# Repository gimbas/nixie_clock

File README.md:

# Nixie Clock

yet another nixie tube clock, esp32 wifi enabled, temperature and humidity sensing, air quality sensing.

## Built With

* esp-idf
* eagle cad

## Authors

* **Rafael Silva** - *initial work* - [gimbas](https://github.com/gimbas)

See also the list of [contributors](https://github.com/gimbas/nixie_clock/graphs/contributors) who participated in this project.

## License

<br />This work is licensed under a <a rel="license" href="http://creativecommons.org/licenses/by-sa/4.0/">Creative Commons Attribution-ShareAlike 4.0 International License</a>.

## Acknowledgments

* HV power supply development and testing - [tonyp7](https://github.com/tonyp7/)

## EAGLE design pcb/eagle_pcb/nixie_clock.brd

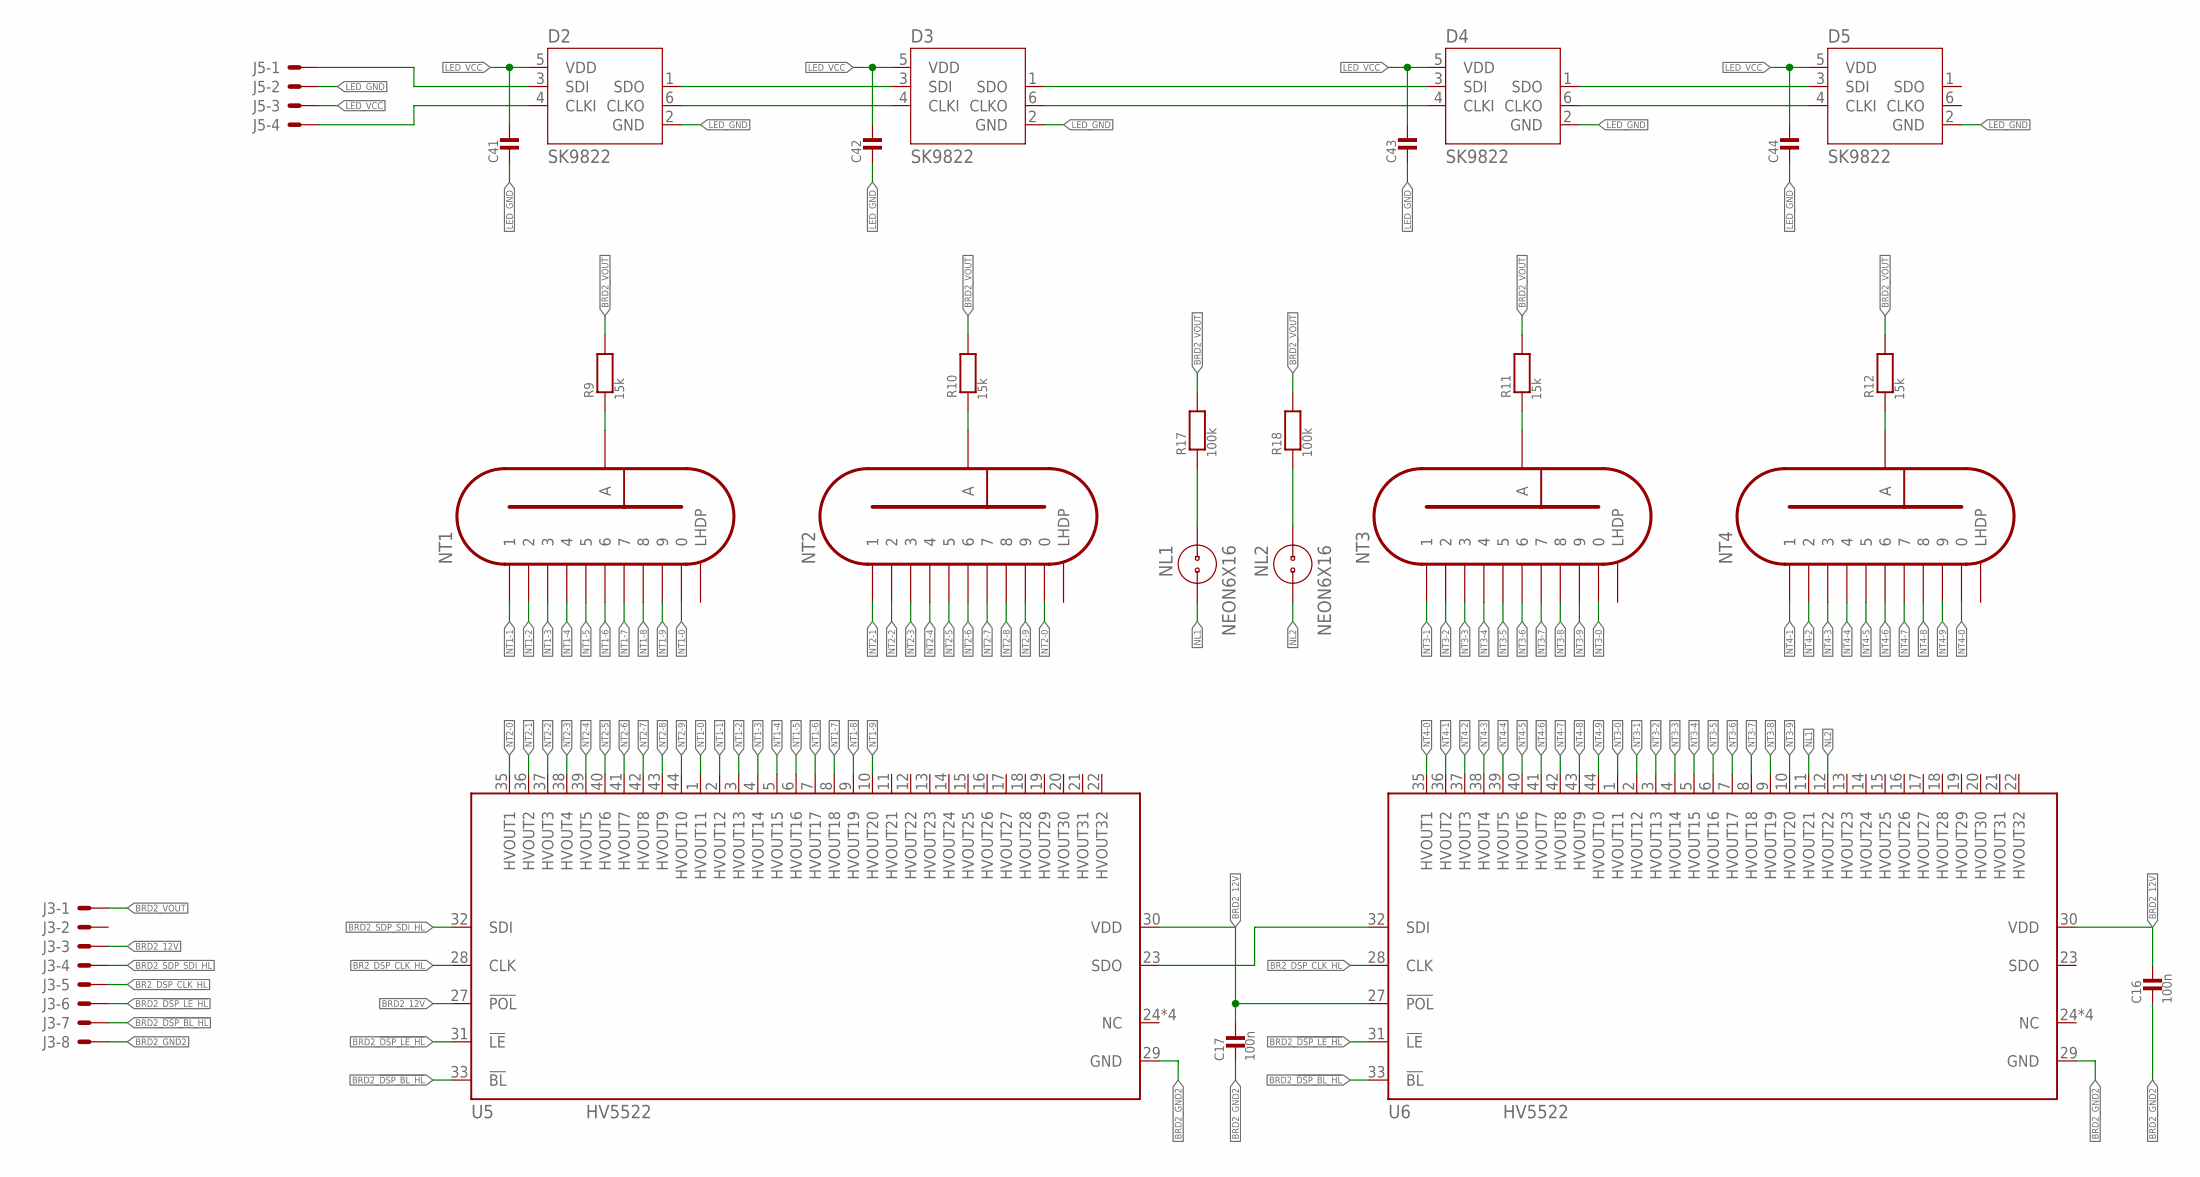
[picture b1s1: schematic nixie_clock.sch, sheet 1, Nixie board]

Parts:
C16, C17: 100n; 0603_WAVE
C41, C42, C43, C44: MLCC0603; 0603_WAVE
D2, D3, D4, D5: SK9822; 2020
J3: 8; 1X8_2.54
J5: 4; 1X4_2.54
NL1, NL2: NEON6X16; NL-6X16
NT1, NT2, NT3, NT4: IN-12B; IN-12
R9, R10, R11, R12: 15k; _1206
R17, R18: 100k; _1206
U5, U6: HV5522; QFP64

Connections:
BR2_DSP_CLK_HL: J3.5, U5.28 (CLK), U6.28 (CLK)
BRD2_12V: C16.P$1, C17.P$1, J3.3, U5.27 (!POL), U5.30 (VDD), U6.27 (!POL), U6.30 (VDD)
BRD2_!DSP_BL_HL: J3.7, U5.33 (!BL), U6.33 (!BL)
BRD2_!DSP_LE_HL: J3.6, U5.31 (!LE), U6.31 (!LE)
BRD2_GND2: C16.P$2, C17.P$2, J3.8, U5.29 (GND), U6.29 (GND)
BRD2_SDP_SDI_HL: J3.4, U5.32 (SDI)
BRD2_VOUT: J3.1, R9.2, R10.2, R11.2, R12.2, R17.2, R18.2
LED_GND: C41.P$2, C42.P$2, C43.P$2, C44.P$2, D2.2 (GND), D3.2 (GND), D4.2 (GND), D5.2 (GND), J5.2
LED_VCC: C41.P$1, C42.P$1, C43.P$1, C44.P$1, D2.5 (VDD), D3.5 (VDD), D4.5 (VDD), D5.5 (VDD), J5.3
unnamed: NT1.A, R9.1
unnamed: NT2.A, R10.1
unnamed: NT3.A, R11.1
unnamed: NT4.A, R12.1
unnamed: NL1.1, R17.1
unnamed: NL2.1, R18.1
unnamed: U5.23 (SDO), U6.32 (SDI)
unnamed: D2.3 (SDI), J5.1
unnamed: D2.4 (CLKI), J5.4
unnamed: D3.1 (SDO), D4.3 (SDI)
unnamed: D3.6 (CLKO), D4.4 (CLKI)
unnamed: D4.6 (CLKO), D5.4 (CLKI)
unnamed: D4.1 (SDO), D5.3 (SDI)
unnamed: D2.6 (CLKO), D3.4 (CLKI)
unnamed: D2.1 (SDO), D3.3 (SDI)
NL1: NL1.2, U6.11 (HVOUT21)
NL2: NL2.2, U6.12 (HVOUT22)
NT1-0: NT1.0, U5.1 (HVOUT11)
NT1-1: NT1.1, U5.2 (HVOUT12)
NT1-2: NT1.2, U5.3 (HVOUT13)
NT1-3: NT1.3, U5.4 (HVOUT14)
NT1-4: NT1.4, U5.5 (HVOUT15)
NT1-5: NT1.5, U5.6 (HVOUT16)
NT1-6: NT1.6, U5.7 (HVOUT17)
NT1-7: NT1.7, U5.8 (HVOUT18)
NT1-8: NT1.8, U5.9 (HVOUT19)
NT1-9: NT1.9, U5.10 (HVOUT20)
NT2-0: NT2.0, U5.35 (HVOUT1)
NT2-1: NT2.1, U5.36 (HVOUT2)
NT2-2: NT2.2, U5.37 (HVOUT3)
NT2-3: NT2.3, U5.38 (HVOUT4)
NT2-4: NT2.4, U5.39 (HVOUT5)
NT2-5: NT2.5, U5.40 (HVOUT6)
NT2-6: NT2.6, U5.41 (HVOUT7)
NT2-7: NT2.7, U5.42 (HVOUT8)
NT2-8: NT2.8, U5.43 (HVOUT9)
NT2-9: NT2.9, U5.44 (HVOUT10)
NT3-0: NT3.0, U6.1 (HVOUT11)
NT3-1: NT3.1, U6.2 (HVOUT12)
NT3-2: NT3.2, U6.3 (HVOUT13)
NT3-3: NT3.3, U6.4 (HVOUT14)
NT3-4: NT3.4, U6.5 (HVOUT15)
NT3-5: NT3.5, U6.6 (HVOUT16)
NT3-6: NT3.6, U6.7 (HVOUT17)
NT3-7: NT3.7, U6.8 (HVOUT18)
NT3-8: NT3.8, U6.9 (HVOUT19)
NT3-9: NT3.9, U6.10 (HVOUT20)
NT4-0: NT4.0, U6.35 (HVOUT1)
NT4-1: NT4.1, U6.36 (HVOUT2)
NT4-2: NT4.2, U6.37 (HVOUT3)
NT4-3: NT4.3, U6.38 (HVOUT4)
NT4-4: NT4.4, U6.39 (HVOUT5)
NT4-5: NT4.5, U6.40 (HVOUT6)
NT4-6: NT4.6, U6.41 (HVOUT7)
NT4-7: NT4.7, U6.42 (HVOUT8)
NT4-8: NT4.8, U6.43 (HVOUT9)
NT4-9: NT4.9, U6.44 (HVOUT10)

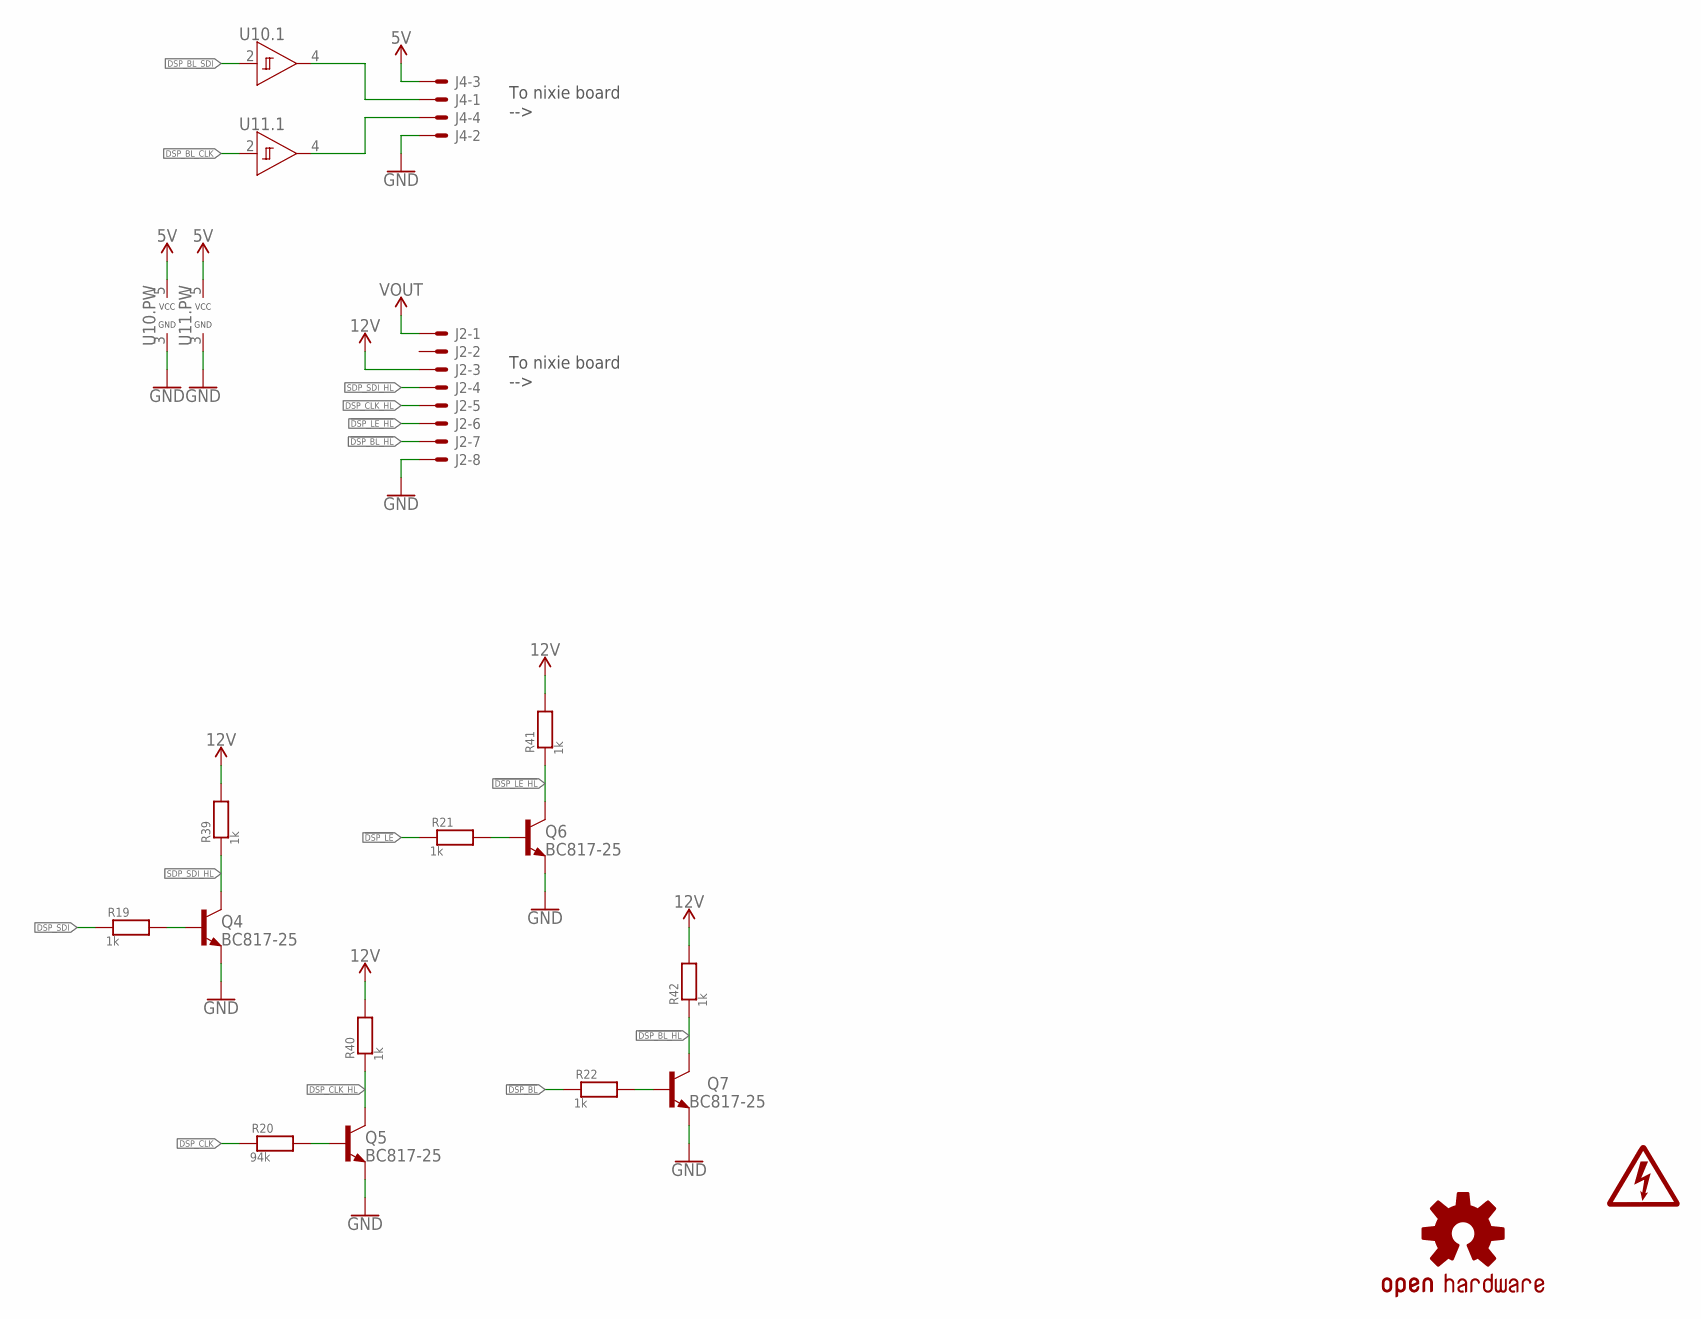
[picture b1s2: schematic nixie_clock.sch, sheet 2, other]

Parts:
J2: 8; 1X8_2.54
J4: 4; 1X4_2.54
LOGO3: OSHW-LOGOL; OSHW-LOGO-L
LOGO6: HV_WARNING
Q4, Q5, Q6, Q7: BC817-25; SOT-23-3
R19, R21, R22, R39, R40, R41, R42: 1k; 0603_WAVE
R20: 94k; 0603_WAVE
U10, U11: 74LVC1G17; SC70-5

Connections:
5V: J4.3, U10.5 (VCC), U11.5 (VCC); also elsewhere on the board
12V: J2.3, R39.P$2, R40.P$2, R41.P$2, R42.P$2; also elsewhere on the board
!DSP_BL: R22.P$1; also elsewhere on the board
!DSP_BL_HL: J2.7, Q7.P$3 (C03), R42.P$1
!DSP_LE: R21.P$1; also elsewhere on the board
!DSP_LE_HL: J2.6, Q6.P$3 (C03), R41.P$1
DSP_BL_CLK: U11.2 (A); also elsewhere on the board
DSP_BL_SDI: U10.2 (A); also elsewhere on the board
DSP_CLK: R20.P$1; also elsewhere on the board
DSP_CLK_HL: J2.5, Q5.P$3 (C03), R40.P$1
DSP_SDI: R19.P$1; also elsewhere on the board
GND: J2.8, J4.2, Q4.P$2 (EM2), Q5.P$2 (EM2), Q6.P$2 (EM2), Q7.P$2 (EM2), U10.3 (GND), U11.3 (GND); also elsewhere on the board
unnamed: Q4.P$1 (BA1), R19.P$2
unnamed: Q5.P$1 (BA1), R20.P$2
unnamed: Q7.P$1 (BA1), R22.P$2
unnamed: Q6.P$1 (BA1), R21.P$2
unnamed: J4.4, U11.4 (Y)
unnamed: J4.1, U10.4 (Y)
SDP_SDI_HL: J2.4, Q4.P$3 (C03), R39.P$1
VOUT: J2.1; also elsewhere on the board

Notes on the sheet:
To nixie board -->

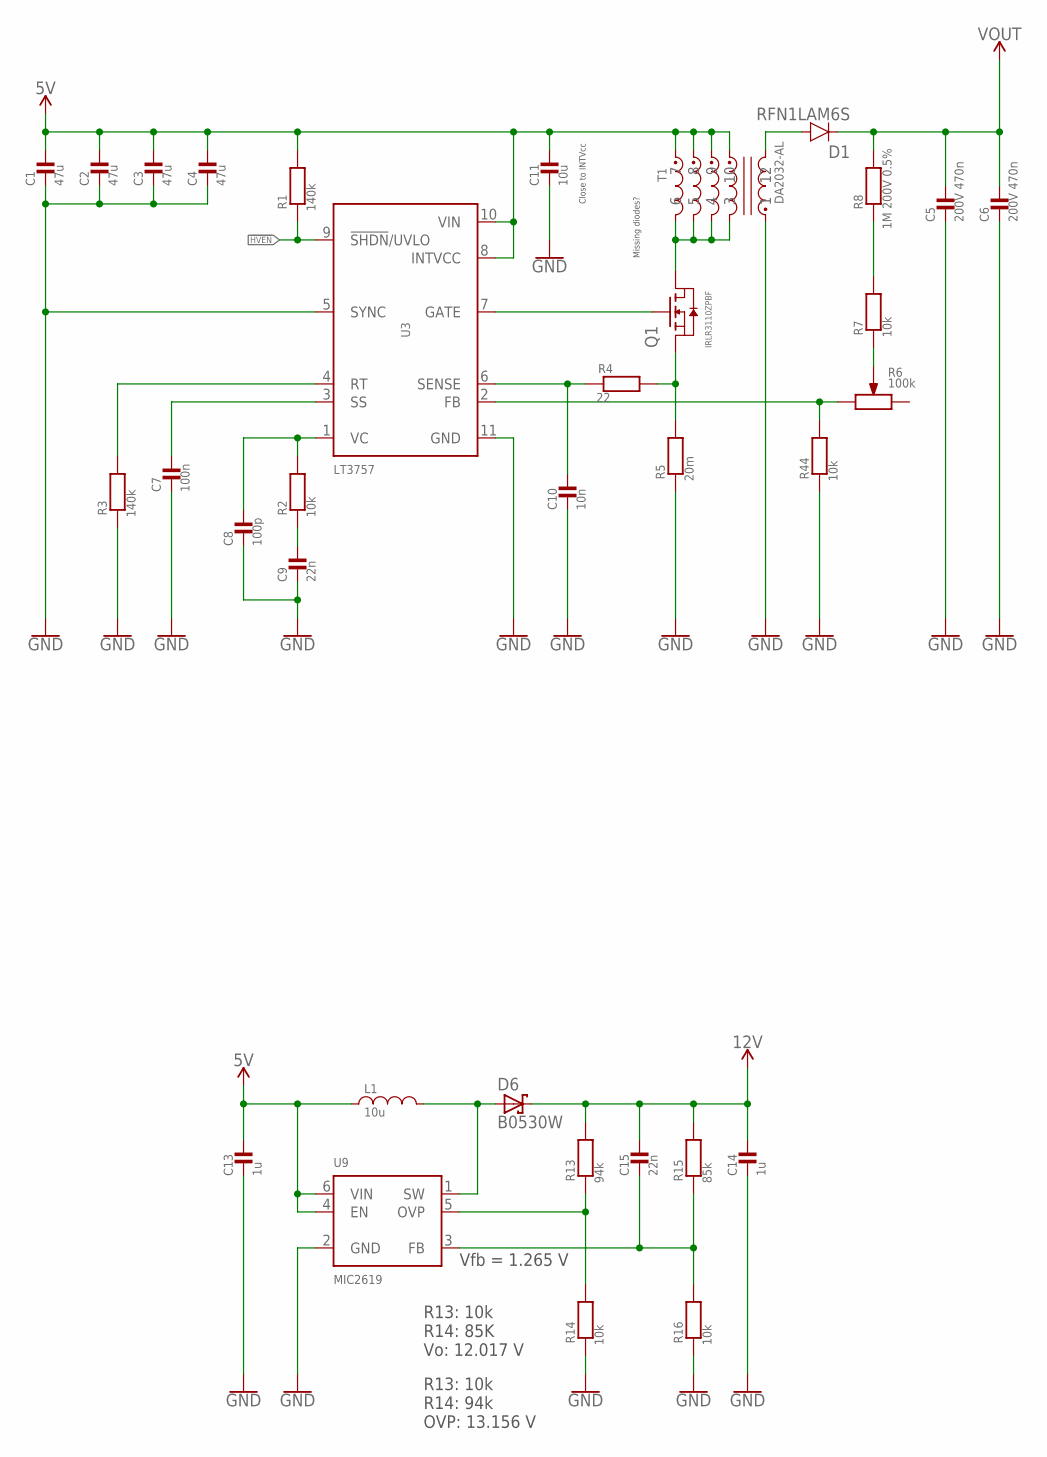
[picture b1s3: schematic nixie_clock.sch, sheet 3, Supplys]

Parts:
C1, C2, C3, C4: 47u; _1210
C5, C6: 200V 470n; _1210
C7: 100n; 0603_WAVE
C8: 100p; 0603_WAVE
C9, C15: 22n; 0603_WAVE
C10: 10n; 0603_WAVE
C11: 10u; 0603_WAVE
C13, C14: 1u; 0603_WAVE
D1: RFN1LAM6S; SOD-128
D6: B0530W; SOD-123
L1: 10u; _1210
Q1: IRLR3110ZPBF; D-PAK
R1, R3: 140k; 0603_WAVE
R2, R7, R14, R16, R44: 10k; 0603_WAVE
R4: 22; 0603_WAVE
R5: 20m; _1206
R6: 100k; TC33X
R8: 1M 200V 0.5%; _1206
R13: 94k; 0603_WAVE
R15: 85k; 0603_WAVE
T1: DA2032-AL
U3: LT3757; DFN10-2
U9: MIC2619; SOT-23-6N

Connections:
5V: C1.1, C2.1, C3.1, C4.1, C11.P$1, C13.P$1, L1.1, R1.P$2, T1.7, T1.8, T1.9, T1.10, U3.8 (INTVCC), U3.10 (VIN), U9.4 (EN), U9.6 (VIN); also elsewhere on the board
12V: C14.P$1, C15.P$1, D6.C, R13.P$2, R15.P$2; also elsewhere on the board
!HVEN: R1.P$1, U3.9 (!SHDN!/UVLO); also elsewhere on the board
GND: C1.2, C2.2, C3.2, C4.2, C5.2, C6.2, C7.P$2, C8.P$2, C9.P$2, C10.P$2, C11.P$2, C13.P$2, C14.P$2, R3.P$1, R5.1, R14.P$1, R16.P$1, R44.P$1, T1.1, U3.5 (SYNC), U3.11 (GND), U9.2 (GND); also elsewhere on the board
unnamed: D1.AN, T1.12
unnamed: C10.P$1, R4.P$1, U3.6 (SENSE)
unnamed: Q1.L (G1), U3.7 (GATE)
unnamed: Q1.P (D1), T1.3, T1.4, T1.5, T1.6
unnamed: Q1.R (S1), R4.P$2, R5.2
unnamed: R6.2, R7.P$1
unnamed: R7.P$2, R8.1
unnamed: C8.P$1, R2.P$2, U3.1 (VC)
unnamed: C9.P$1, R2.P$1
unnamed: C7.P$1, U3.3 (SS)
unnamed: R3.P$2, U3.4 (RT)
unnamed: D6.A, L1.2, U9.1 (SW)
unnamed: R13.P$1, R14.P$2, U9.5 (OVP)
unnamed: C15.P$2, R15.P$1, R16.P$2, U9.3 (FB)
unnamed: R6.3, R44.P$2, U3.2 (FB)
VOUT: C5.1, C6.1, D1.CAT, R8.2; also elsewhere on the board

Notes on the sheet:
Close to INTVcc
Missing diodes?
Vfb = 1.265 V
R13: 10k R14: 85K Vo: 12.017 V
R13: 10k R14: 94k OVP: 13.156 V

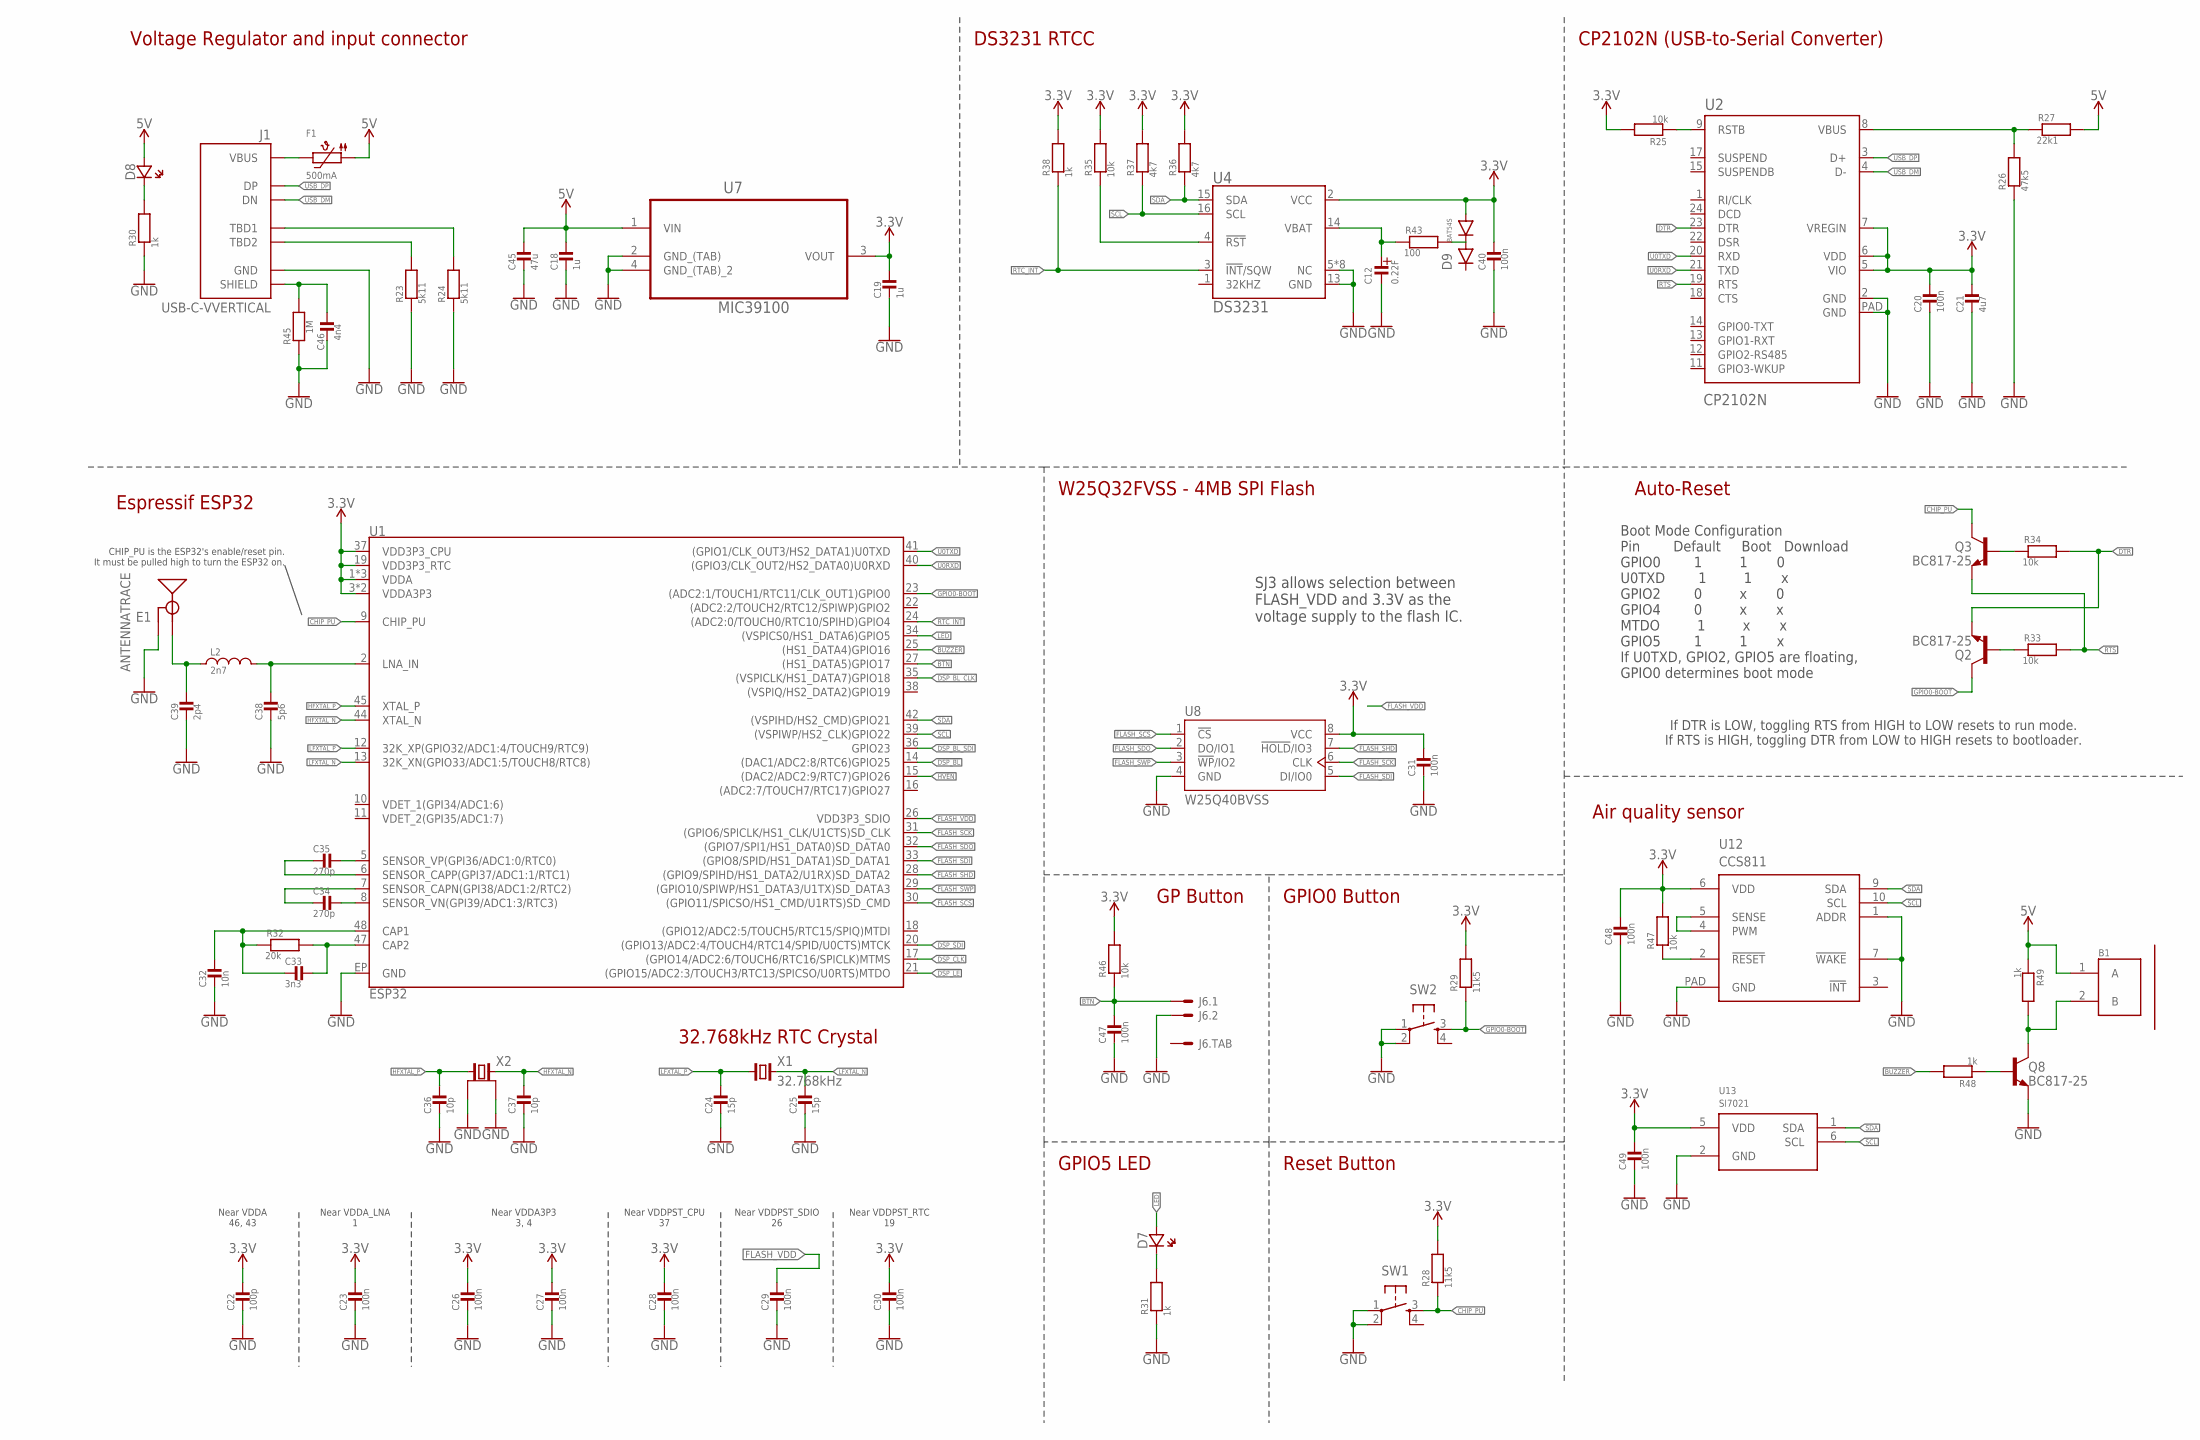
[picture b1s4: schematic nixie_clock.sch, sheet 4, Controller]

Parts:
B1: PKLCS1212E2400-R1; BUZZ_PIEZO_SMD
C12: 0.22F; DSK-614/621
C18, C19: 1u; 0603_WAVE
C20, C23, C26, C27, C28, C29, C30, C31, C40, C47, C48, C49: 100n; 0603_WAVE
C21: 4u7; 0603_WAVE
C22: 100p; 0603_WAVE
C24, C25: 15p; 0603_WAVE
C32: 10n; 0603_WAVE
C33: 3n3; 0603_WAVE
C34, C35: 270p; 0603_WAVE
C36, C37: 10p; 0603_WAVE
C38: 5p6; 0603_WAVE
C39: 2p4; 0603_WAVE
C45: 47u; _1210
C46: 4n4; 0603_WAVE
D7, D8: LED0603; CHIPLED_0603
D9: BAT54S; SOT-23-3
E1: ANTENNATRACE; TRACE_ANTENNA_2.4GHZ_25.7MM
F1: 500mA; 0805
J1: USB-C-VVERTICAL; USB-C-V
J6: PH-2; JST_PH_SMD_2
L2: 2n7; _0603
Q2, Q3, Q8: BC817-25; SOT-23-3
R23, R24: 5k11; 0603_WAVE
R25, R33, R34, R35, R46, R47: 10k; 0603_WAVE
R26: 47k5; 0603_WAVE
R27: 22k1; 0603_WAVE
R28, R29: 11k5; 0603_WAVE
R30, R31, R38, R48, R49: 1k; 0603_WAVE
R32: 20k; 0603_WAVE
R36, R37: 4k7; 0603_WAVE
R43: 100; 0603_WAVE
R45: 1M; 0603_WAVE
SW1, SW2: PUSH_BUTTON3X4X2; 3X4X2
U1: ESP32; QFN48-0.4MM
U2: CP2102N; QFN24
U4: DS3231; SOIC-16
U7: MIC39100; SOT230P700X180-4N
U8: W25Q40BVSS; SO08-SS
U12: CCS811; LGA10
U13: SI7021; DFN6
X1: 32.768kHz; 2-SMD-3215
X2: 26MHz; 4-SMD-3225

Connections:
3.3V: C19.P$1, C20.P$1, C21.P$1, C22.P$1, C23.P$1, C26.P$1, C27.P$1, C28.P$1, C30.P$1, C31.P$1, C40.P$1, C48.P$1, C49.P$1, D9.P$1 (1), R25.P$2, R28.P$2, R29.P$2, R35.P$2, R36.P$2, R37.P$2, R38.P$2, R46.P$2, R47.P$2, U1.1 (VDDA), U1.3 (VDDA3P3), U1.4 (VDDA3P3), U1.19 (VDD3P3_RTC), U1.37 (VDD3P3_CPU), U1.43 (VDDA), U1.46 (VDDA), U2.5 (VIO), U2.6 (VDD), U2.7 (VREGIN), U4.2 (VCC), U7.3 (VOUT), U8.8 (VCC), U12.6 (VDD), U13.5 (VDD)
5V: B1.1 (A), C18.P$1, C45.1, D8.A (AN), F1.1, R27.P$2, R49.P$1, U7.1 (VIN); also elsewhere on the board
!DSP_BL: U1.14 ((DAC1/ADC2:8/RTC6)GPIO25); also elsewhere on the board
!DSP_LE: U1.21 ((GPIO15/ADC2:3/TOUCH3/RTC13/SPICSO/U0RT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); also elsewhere on the board
!HVEN: U1.15 ((DAC2/ADC2:9/RTC7)GPIO26); also elsewhere on the board
BTN: C47.P$1, J6.1, R46.P$1, U1.27 ((HS1_DATA5)GPIO17)
BUZZER: R48.P$2, U1.25 ((HS1_DATA4)GPIO16)
CHIP_PU: Q3.P$3 (C03), R28.P$1, SW1.3 (4), U1.9 (CHIP_PU)
DSP_BL_CLK: U1.35 ((VSPICLK/HS1_DATA7)GPIO18); also elsewhere on the board
DSP_BL_SDI: U1.36 (GPIO23); also elsewhere on the board
DSP_CLK: U1.17 ((GPIO14/ADC2:6/TOUCH6/RTC16/SPICLK)MTMS); also elsewhere on the board
DSP_SDI: U1.20 ((GPIO13/ADC2:4/TOUCH4/RTC14/SPID/U0CTS)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); also elsewhere on the board
DTR: Q2.P$2 (EM2), R34.P$2, U2.23 (DTR)
FLASH_SCK: U1.31 ((GPIO6/SPICLK/HS1_CLK/U1CTS)SD_CLK), U8.6 (CLK)
FLASH_SCS: U1.30 ((GPIO11/SPICSO/HS1_CMD/U1RTS)SD_CMD), U8.1 (!CS!)
FLASH_SDI: U1.33 ((GPIO8/SPID/HS1_DATA1)SD_DATA1), U8.5 (DI/IO0)
FLASH_SDO: U1.32 ((GPIO7/SPI1/HS1_DATA0)SD_DATA0), U8.2 (DO/IO1)
FLASH_SHD: U1.28 ((GPIO9/SPIHD/HS1_DATA2/U1RX)SD_DATA2), U8.7 (!HOLD!/IO3)
FLASH_SWP: U1.29 ((GPIO10/SPIWP/HS1_DATA3/U1TX)SD_DATA3), U8.3 (!WP!/IO2)
FLASH_VDD: C29.P$1, U1.26 (VDD3P3_SDIO)
GND: C12.2 (CA), C18.P$2, C19.P$2, C20.P$2, C21.P$2, C22.P$2, C23.P$2, C24.P$2, C25.P$2, C26.P$2, C27.P$2, C28.P$2, C29.P$2, C30.P$2, C31.P$2, C32.P$2, C36.P$2, C37.P$2, C38.P$2, C39.P$2, C40.P$2, C45.2, C46.P$2, C47.P$2, C48.P$2, C49.P$2, E1.GND, E1.GND2 (GND), J1.1 (GND), J1.2 (GND), J1.15 (GND), J1.16 (GND), J6.2, Q8.P$2 (EM2), R23.P$1, R24.P$1, R26.P$1, R30.P$1, R31.P$1, R45.P$1, SW1.1, SW1.2, SW2.1, SW2.2, U1.EP (GND), U2.2 (GND), U2.PAD (GND), U4.5 (NC), U4.6 (NC), U4.7 (NC), U4.8 (NC), U4.9 (NC), U4.10 (NC), U4.11 (NC), U4.12 (NC), U4.13 (GND), U7.2 (GND_(TAB)), U7.4 (GND_(TAB)_2), U8.4 (GND), U12.1 (ADDR), U12.7 (!WAKE), U12.PAD (GND), U13.2 (GND), X2.1 (GND), X2.3 (GND); also elsewhere on the board
GPIO0-BOOT: Q2.P$3 (C03), R29.P$1, SW2.3 (4), U1.23 ((ADC2:1/TOUCH1/RTC11/CLK_OUT1)GPIO0)
HFXTAL_N: C37.P$1, U1.44 (XTAL_N), X2.4 (2)
HFXTAL_P: C36.P$1, U1.45 (XTAL_P), X2.2 (1)
LED: D7.A (AN), U1.34 ((VSPICS0/HS1_DATA6)GPIO5)
LFXTAL_N: C25.P$1, U1.13 (32K_XN(GPIO33/ADC1:5/TOUCH8/RTC8)), X1.2
LFXTAL_P: C24.P$1, U1.12 (32K_XP(GPIO32/ADC1:4/TOUCH9/RTC9)), X1.1
unnamed: C39.P$1, E1.ANT (SIGNAL), L2.1
unnamed: D9.P$3 (3), R43.P$2
unnamed: C46.P$1, J1.S1 (SHIELD), J1.S2 (SHIELD), J1.S3 (SHIELD), J1.S4 (SHIELD), R45.P$2
unnamed: R47.P$1, U12.2 (!RESET)
unnamed: U12.4 (PWM), U12.5 (SENSE)
unnamed: B1.2 (B), Q8.P$3 (C03), R49.P$2
unnamed: Q8.P$1 (BA1), R48.P$1
unnamed: F1.2, J1.3 (VBUS), J1.4 (VBUS), J1.13 (VBUS), J1.14 (VBUS)
unnamed: J1.6 (TBD2), R23.P$2
unnamed: J1.11 (TBD1), R24.P$2
unnamed: R25.P$1, U2.9 (RSTB)
unnamed: D8.C (CA), R30.P$2
unnamed: R26.P$2, R27.P$1, U2.8 (VBUS)
unnamed: D7.C (CA), R31.P$2
unnamed: C33.P$1, R32.P$2, U1.47 (CAP2)
unnamed: C34.P$1, U1.8 (SENSOR_VN(GPI39/ADC1:3/RTC3))
unnamed: C32.P$1, C33.P$2, R32.P$1, U1.48 (CAP1)
unnamed: C35.P$1, U1.5 (SENSOR_VP(GPI36/ADC1:0/RTC0))
unnamed: C34.P$2, U1.7 (SENSOR_CAPN(GPI38/ADC1:2/RTC2))
unnamed: C35.P$2, U1.6 (SENSOR_CAPP(GPI37/ADC1:1/RTC1))
unnamed: C38.P$1, L2.2, U1.2 (LNA_IN)
unnamed: Q2.P$1 (BA1), R33.P$1
unnamed: Q3.P$1 (BA1), R34.P$1
unnamed: C12.1 (AN), R43.P$1, U4.14 (VBAT)
unnamed: R35.P$1, U4.4 (!RST)
RTC_INT: R38.P$1, U1.24 ((ADC2:0/TOUCH0/RTC10/SPIHD)GPIO4), U4.3 (!INT!/SQW)
RTS: Q3.P$2 (EM2), R33.P$2, U2.19 (RTS)
SCL: R37.P$1, U1.39 ((VSPIWP/HS2_CLK)GPIO22), U4.16 (SCL), U12.10 (SCL), U13.6 (SCL)
SDA: R36.P$1, U1.42 ((VSPIHD/HS2_CMD)GPIO21), U4.15 (SDA), U12.9 (SDA), U13.1 (SDA)
U0RXD: U1.40 ((GPIO3/CLK_OUT2/HS2_DATA0)U0RXD), U2.21 (TXD)
U0TXD: U1.41 ((GPIO1/CLK_OUT3/HS2_DATA1)U0TXD), U2.20 (RXD)
USB_DM: J1.7 (DN), J1.10 (DN), U2.4 (D-)
USB_DP: J1.8 (DP), J1.9 (DP), U2.3 (D+)

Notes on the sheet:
Near VDDA 46, 43
Near VDDA_LNA 1
Near VDDA3P3 3, 4
Near VDDPST_CPU 37
Near VDDPST_SDIO 26
Near VDDPST_RTC 19
Boot Mode Configuration Pin Default Boot Download GPIO0 1 1 0 U0TXD 1 1 x GPIO2 0 x 0 GPIO4 0 x x MTDO 1 x x GPIO5 1 1 x If U0TXD, GPIO2, GPIO5 are floating, GPIO0 determines boot mode
CP2102N (USB-to-Serial Converter)
Voltage Regulator and input connector
Auto-Reset
Espressif ESP32
W25Q32FVSS - 4MB SPI Flash
32.768kHz RTC Crystal
GPIO0 Button
Reset Button
GPIO5 LED
SJ3 allows selection between FLASH_VDD and 3.3V as the voltage supply to the flash IC.
If DTR is LOW, toggling RTS from HIGH to LOW resets to run mode. If RTS is HIGH, toggling DTR from LOW to HIGH resets to bootloader.
CHIP_PU is the ESP32's enable/reset pin. It must be pulled high to turn the ESP32 on.
DS3231 RTCC
GP Button
Air quality sensor

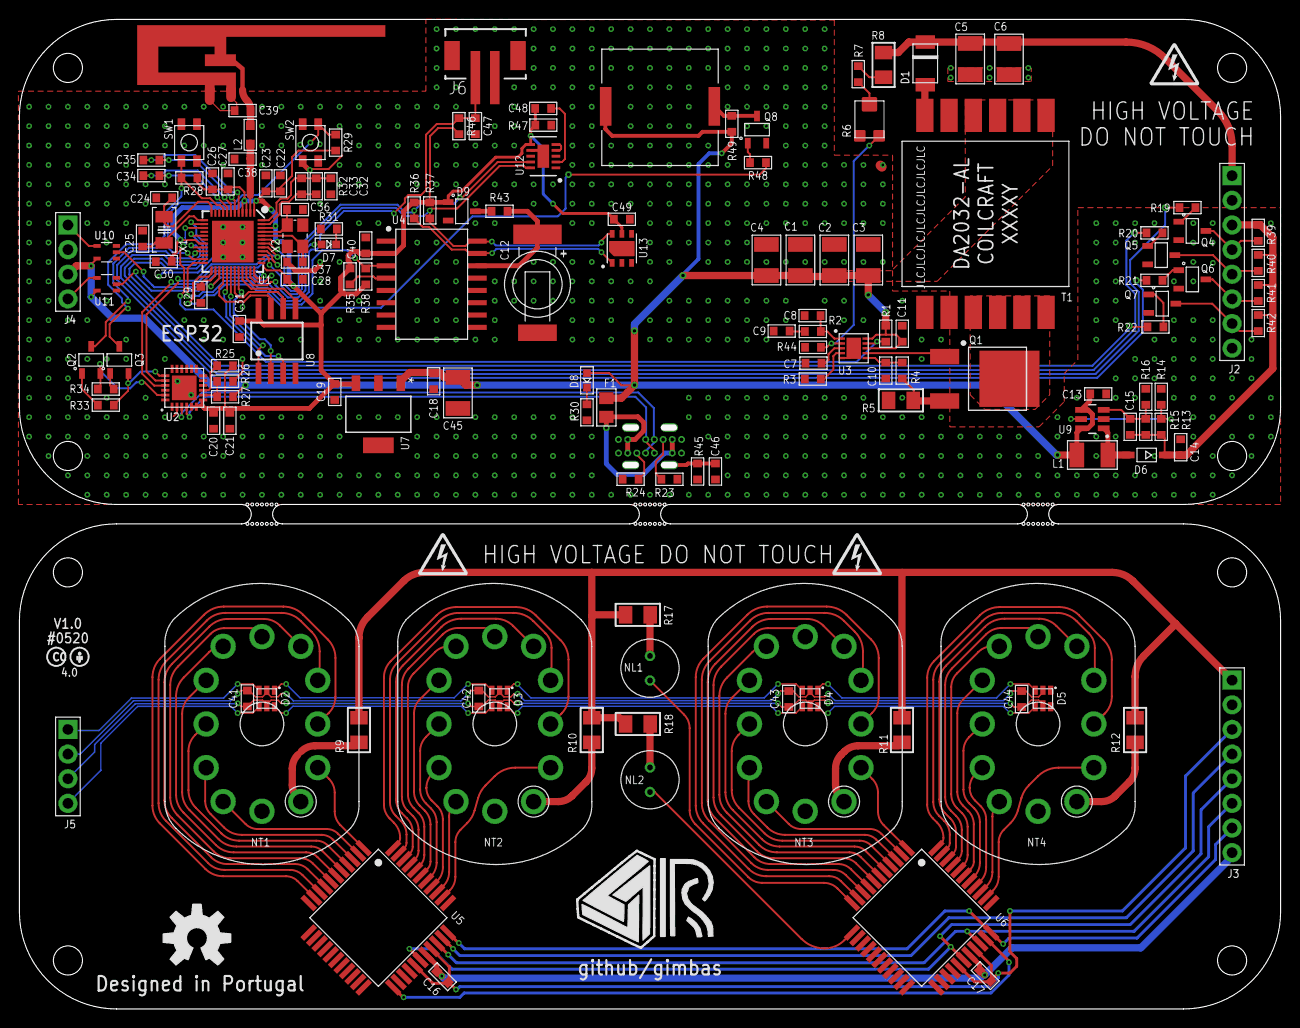
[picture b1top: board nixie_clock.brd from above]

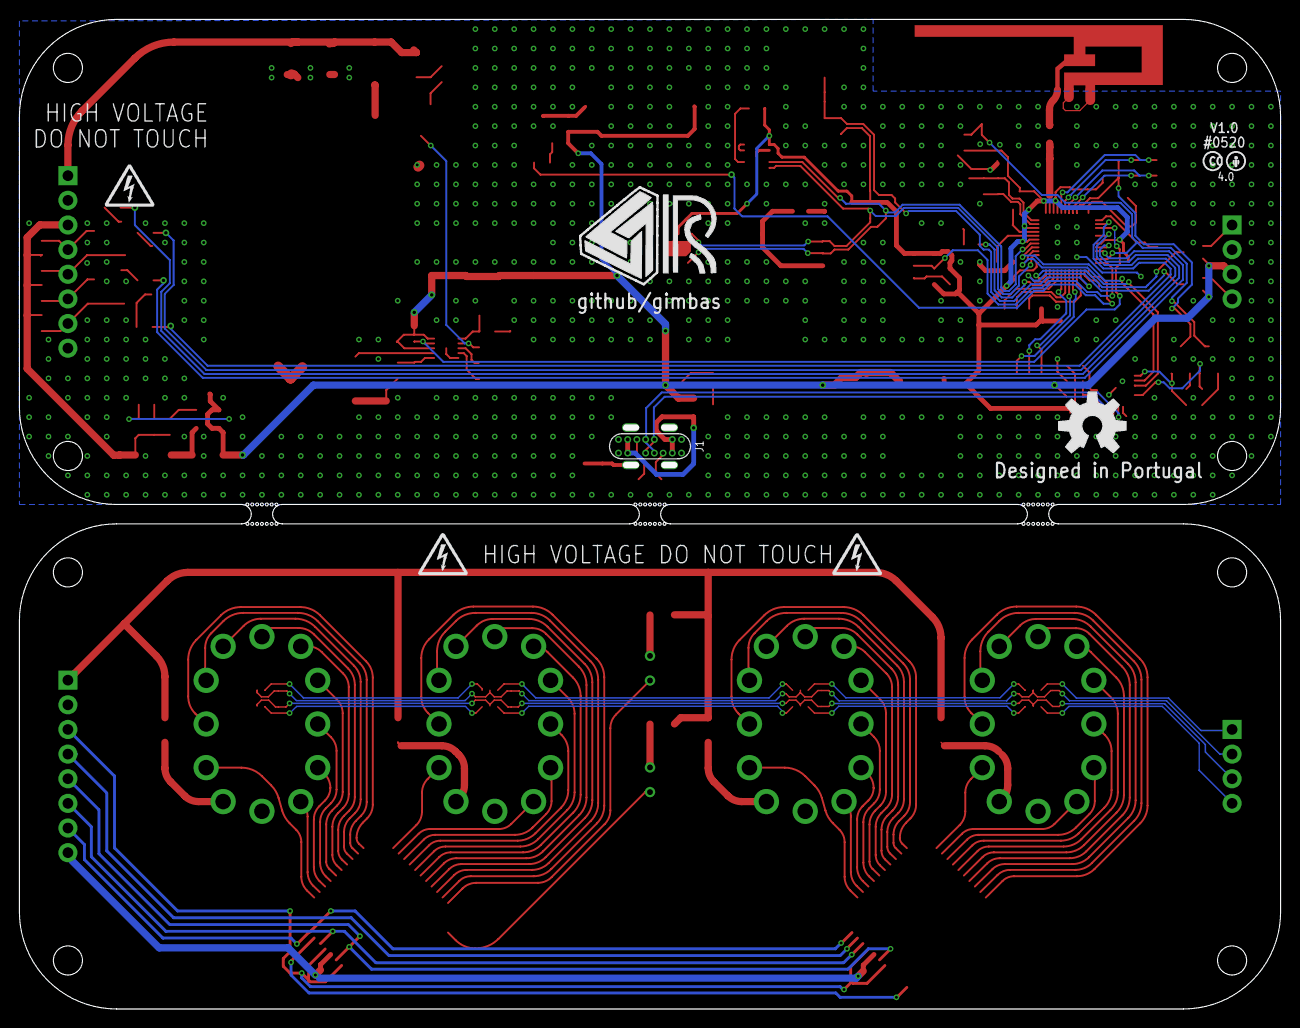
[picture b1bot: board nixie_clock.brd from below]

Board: 2 copper layers, 129.4 x 101.3 mm, 160 parts (6 on the bottom side), 153 nets.

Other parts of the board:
LOGO1, LOGO4, LOGO5, LOGO7, LOGO13: HV_WARNING
LOGO2: OSHW-LOGOL; OSHW-LOGO-L
U$1, U$3: RAFAEL_SILVA_10MM_ALT

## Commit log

2019-11-29 sch and pcb outline
2019-12-04 rough pcb done
2019-12-04 finished board -TODO change usb connector
2019-12-05 changed usb connector
2019-12-14 fix typo
2020-01-18 corrected usb pd resistor values
2020-01-23 small fixes
2020-01-27 ready for production
2020-01-27 LICENSE update
2020-01-27 added buzzer
2020-07-30 stash

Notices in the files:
pcb/eagle_pcb/nixie_clock.sch:
LICENSE: Attribution-ShareAlike 4.0 International (CC BY-SA 4.0)
pcb/nixie_clock/nixie_clock.sch:
LICENSE: MIT
